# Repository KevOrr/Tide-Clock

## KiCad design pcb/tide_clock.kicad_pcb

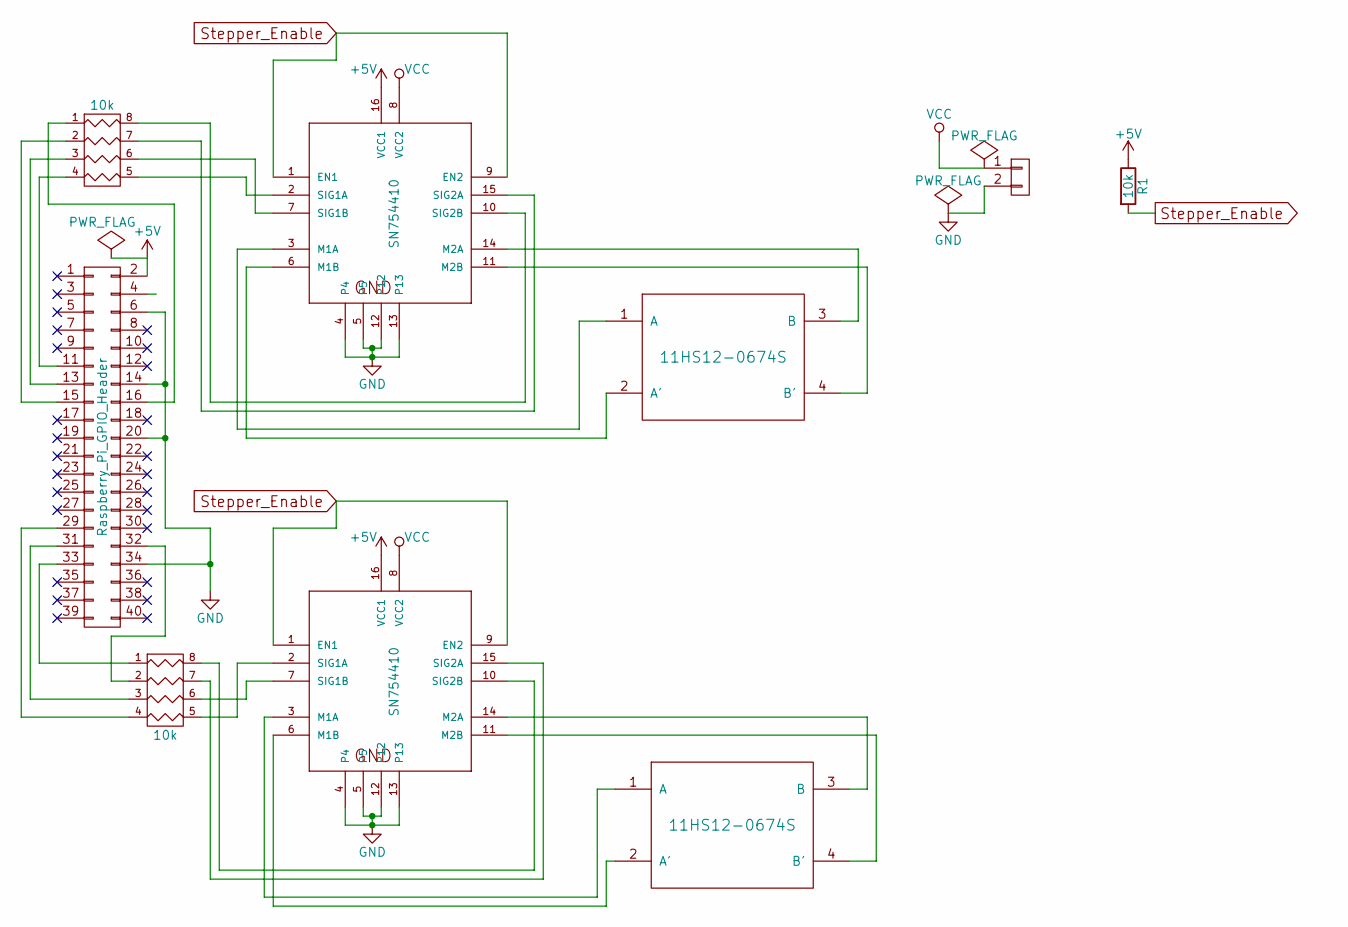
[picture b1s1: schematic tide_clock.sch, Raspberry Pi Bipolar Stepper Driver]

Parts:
IC1, IC2: SN754410; DIP-16_W7.62mm
M1, M2: 11HS12-0674S; Pin_Header_Angled_1x04
P1: Raspberry_Pi_GPIO_Header; Socket_Strip_Straight_2x20
P2: CONN_01X02; Pin_Header_Angled_1x02
R1: 10k; R_1206_HandSoldering
RP1, RP2: 10k; R_Array_Convex_4x1206

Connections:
+5V: IC1.16 (VCC1), IC2.16 (VCC1), P1.2 (+5V), R1.1
GND: IC1.4, IC1.5, IC1.12, IC1.13, IC2.4, IC2.5, IC2.12, IC2.13, P1.6 (GND), P1.14 (GND), P1.20 (GND), P1.34 (GND), P2.2
unnamed: IC1.2 (SIG1A), RP2.5 (R4)
unnamed: IC1.3 (M1A), M1.1 (A)
unnamed: IC1.6 (M1B), M1.2 (A')
unnamed: IC1.7 (SIG1B), RP2.6 (R3)
unnamed: IC1.10 (SIG2B), RP2.8 (R1)
unnamed: IC1.11 (M2B), M1.4 (B')
unnamed: IC1.14 (M2A), M1.3 (B)
unnamed: IC1.15 (SIG2A), RP2.7 (R2)
unnamed: IC2.2 (SIG1A), RP1.5 (R4)
unnamed: IC2.3 (M1A), M2.1 (A)
unnamed: IC2.6 (M1B), M2.2 (A')
unnamed: IC2.7 (SIG1B), RP1.6 (R3)
unnamed: IC2.10 (SIG2B), RP1.8 (R1)
unnamed: IC2.11 (M2B), M2.4 (B')
unnamed: IC2.14 (M2A), M2.3 (B)
unnamed: IC2.15 (SIG2A), RP1.7 (R2)
unnamed: P1.11 (GPIO17_(GEN0)), RP2.4
unnamed: P1.13 (GPIO27_(GEN2)), RP2.3
unnamed: P1.15 (GPIO22_(GEN3)), RP2.2
unnamed: P1.16 (GPIO23_(GEN4)), RP2.1
unnamed: P1.29 (GPIO05), RP1.4
unnamed: P1.31 (GPIO06), RP1.3
unnamed: P1.32 (GPIO12), RP1.2
unnamed: P1.33 (GPIO13), RP1.1
Stepper_Enable: IC1.1 (EN1), IC1.9 (EN2), IC2.1 (EN1), IC2.9 (EN2), R1.2
VCC: IC1.8 (VCC2), IC2.8 (VCC2), P2.1

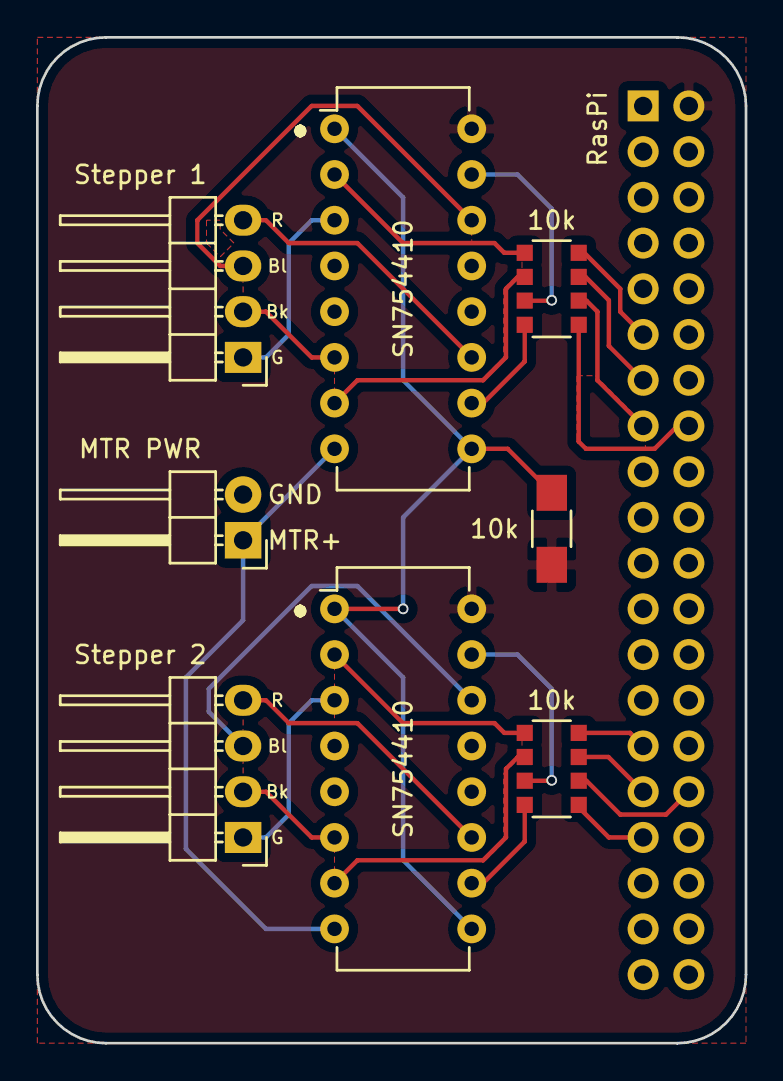
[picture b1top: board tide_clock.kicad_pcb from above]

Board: 2 copper layers, 39.4 x 55.9 mm, 9 parts (1 on the bottom side), 28 nets.

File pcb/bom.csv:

"Id";"Designator";"Package";"Quantity";"Designation";"Supplier and ref";
1;"P1";"Socket_Strip_Straight_2x20";1;"Raspberry_Pi_GPIO_Header";;;
2;"IC1,IC2";"DIP-16_W7.62mm";2;"SN754410";;;
3;"RP1,RP2";"R_Array_Convex_4x1206";2;"10k";;;
4;"M2,M1";"Pin_Header_Angled_1x04";2;"11HS12-0674S";;;
5;"R1";"R_1206_HandSoldering";1;"10k";;;
6;"P2";"Pin_Header_Angled_1x02";1;"CONN_01X02";;;

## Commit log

2016-06-29 Further implemented connectivity and setup
    * Added more string resources, moved some constants to Util class
2016-07-01 Updated target sdk version to 24, updated gradle
2016-07-01 Fixed Charset lookup for sdk < KitKat
2016-07-01 Fixed generics warning, extracted TextView string
2016-07-20 Moved NOAA station scraper/selector to scripts/
2016-07-22 Added stepper driver code, now depends on RPi.GPIO
2016-07-22 Updated .gitignore
2016-07-22 moved scripts to control/
2016-07-22 Added main script, changed format of stations.json
2016-07-22 Fixed a few more typos
2016-07-22 Fixed bug in steppers.py
2016-07-22 Java brainfart
2016-07-25 Added properties, proper speed handling, run thread
2016-07-25 DEBUG should be False
2016-07-25 Fixed incorrect stepper drive pattern
2016-07-25 Added data -> stepper code, changed power to property
2016-08-10 Added MSW swell height, slight refactoring
2016-08-13 Added KiCAD project for the stepper driver board
    This includes the schematic, generated netlist, pcb design, necessary
    libraries, renders, and a BOM. It does not include Gerber plots,
    since these are essentially builds that can be generatred from
    the kicad_pcb file.
